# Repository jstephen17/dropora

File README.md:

# dropora
An automated system designed to securely receive and store parcels when you are away.

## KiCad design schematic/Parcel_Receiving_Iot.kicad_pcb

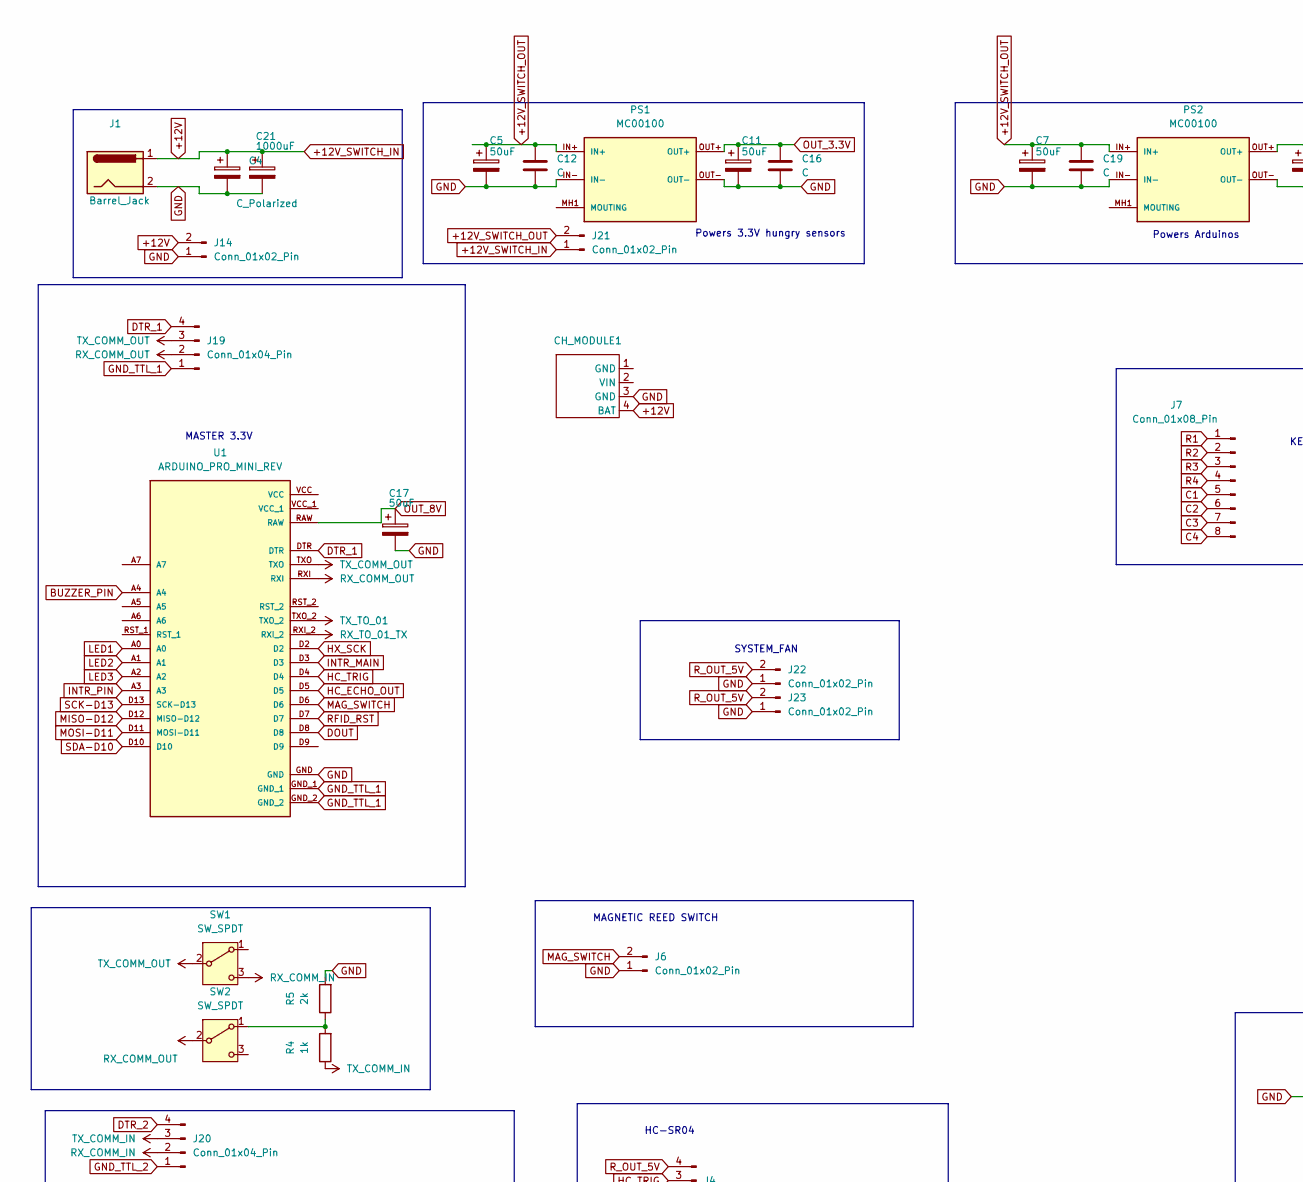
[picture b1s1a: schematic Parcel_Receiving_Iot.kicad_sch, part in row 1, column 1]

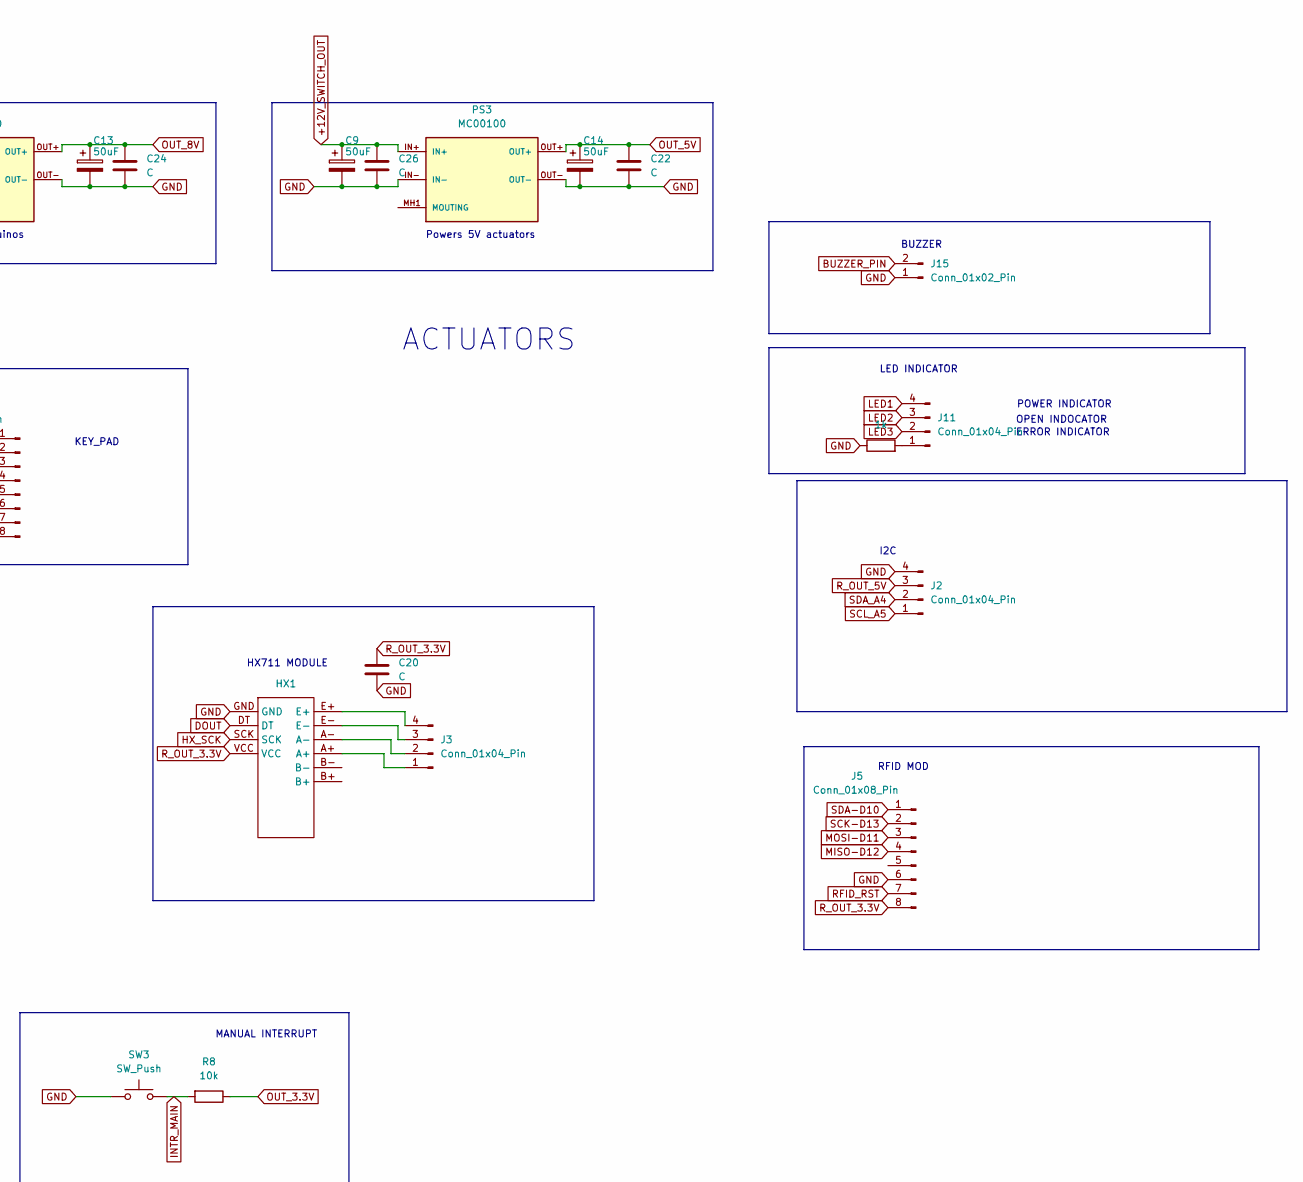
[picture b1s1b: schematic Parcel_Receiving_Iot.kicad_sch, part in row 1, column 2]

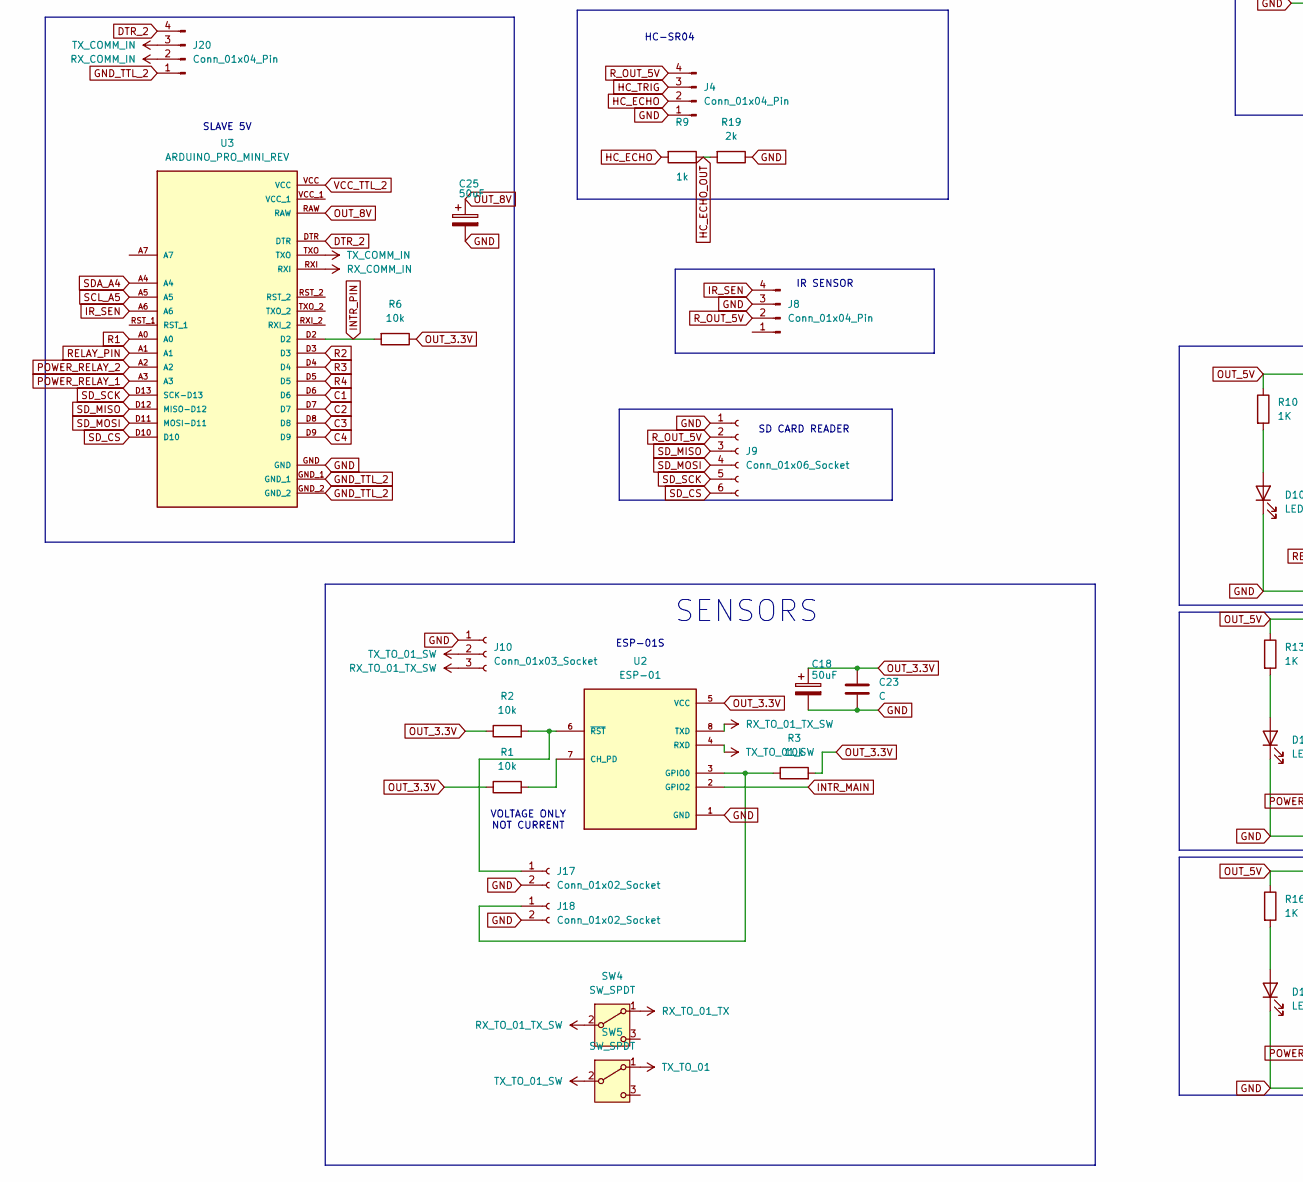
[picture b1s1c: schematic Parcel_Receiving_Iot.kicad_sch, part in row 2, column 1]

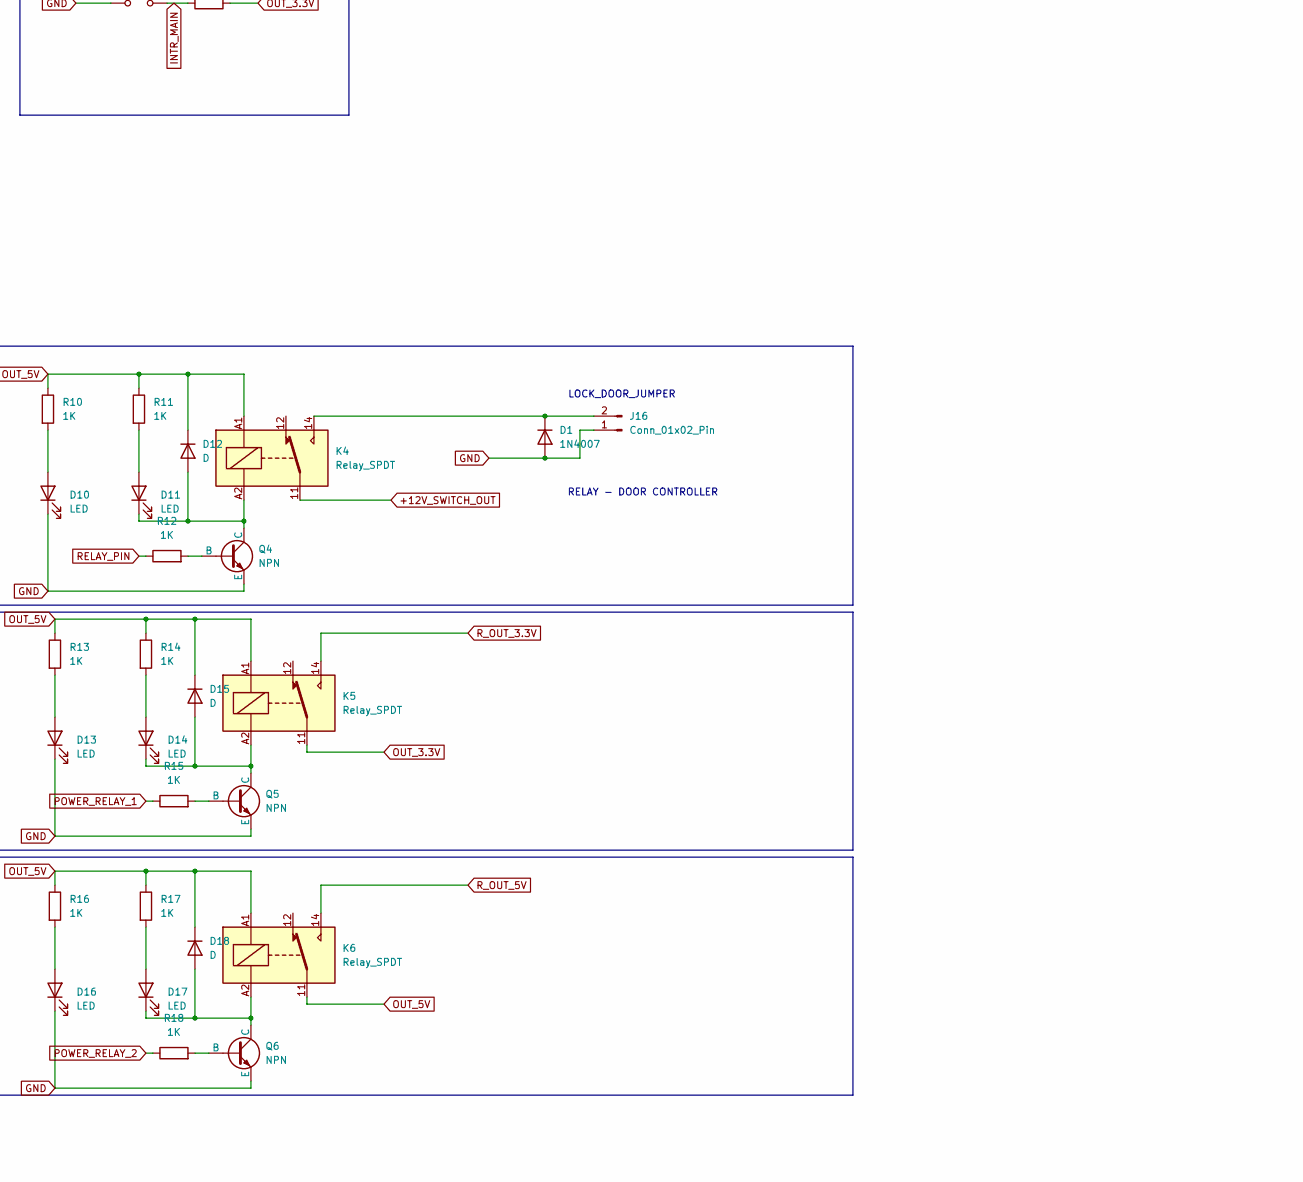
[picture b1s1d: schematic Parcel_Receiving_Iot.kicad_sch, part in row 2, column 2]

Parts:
C4: C_Polarized; CP_Radial_D5.0mm_P2.00mm
C5, C7, C9, C11, C13, C14, C18: 50uF; CP_Radial_D8.0mm_P2.50mm
C12, C16, C19, C20, C22, C23, C24, C26: C; C_Disc_D5.0mm_W2.5mm_P2.50mm
C17, C25: 50uF; CP_Radial_D5.0mm_P2.00mm
C21: 1000uF; CP_Radial_D10.0mm_P5.00mm
CH_MODULE1: CHARGING_MODULE
D1: 1N4007; D_DO-41_SOD81_P10.16mm_Horizontal
D10, D11, D13, D14, D16, D17: LED; LED_D3.0mm
D12, D15, D18: D; D_DO-15_P10.16mm_Horizontal
HX1: HX711_MODULE
J1: Barrel_Jack; BarrelJack_Horizontal
J2, J3, J4, J8, J11: Conn_01x04_Pin; JST_PH_B4B-PH-K_1x04_P2.00mm_Vertical
J5, J7: Conn_01x08_Pin; JST_PH_B8B-PH-K_1x08_P2.00mm_Vertical
J6, J15, J16: Conn_01x02_Pin; JST_PH_B2B-PH-K_1x02_P2.00mm_Vertical
J9: Conn_01x06_Socket; PinHeader_1x06_P2.54mm_Vertical
J10: Conn_01x03_Socket; PinHeader_1x03_P2.54mm_Vertical
J14, J21, J22, J23: Conn_01x02_Pin; JST_XH_B2B-XH-A_1x02_P2.50mm_Vertical
J17, J18: Conn_01x02_Socket; PinHeader_1x02_P2.54mm_Vertical
J19, J20: Conn_01x04_Pin; PinHeader_1x04_P2.54mm_Vertical
K4, K5, K6: Relay_SPDT; Relay_SPDT_SANYOU_SRD_Series_Form_C
PS1, PS2, PS3: MC00100; CONV_MC00100; PARTREV NA
Q4, Q5, Q6: NPN; TO-92L_Inline_Wide
R1, R2, R3, R6, R8: 10k; R_Axial_DIN0207_L6.3mm_D2.5mm_P10.16mm_Horizontal
R4, R7, R9: 1k; R_Axial_DIN0207_L6.3mm_D2.5mm_P10.16mm_Horizontal
R5, R19: 2k; R_Axial_DIN0207_L6.3mm_D2.5mm_P10.16mm_Horizontal
R10, R11, R12, R13, R14, R15, R16, R17, R18: 1K; R_Axial_DIN0207_L6.3mm_D2.5mm_P7.62mm_Horizontal
SW1, SW2, SW4, SW5: SW_SPDT; SW_Slide_SPDT_Straight_CK_OS102011MS2Q
SW3: SW_Push; SW_PUSH_6mm_H5mm
U1, U3: ARDUINO_PRO_MINI_REV; MODULE_ARDUINO_PRO_MINI_REV; PARTREV N/A
U2: ESP-01; MODULE_ESP-01; PARTREV 1.0

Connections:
+12V: C4.1, C21.1, CH_MODULE1.4 (BAT), J1.1, J14.2, J21.1
+12V_SWITCH_OUT: C5.1, C7.1, C9.1, C12.1, C19.1, C26.1, J21.2, K4.11, PS1.IN+, PS2.IN+, PS3.IN+
BUZZER_PIN: J15.2, U1.A4
C1: J7.5, U3.D6
C2: J7.6, U3.D7
C3: J7.7, U3.D8
C4: J7.8, U3.D9
DOUT: HX1.DT, U1.D8
DTR_1: J19.4, U1.DTR
DTR_2: J20.4, U3.DTR
GND: C4.2, C5.2, C7.2, C9.2, C11.2, C12.2, C13.2, C14.2, C16.2, C17.2, C18.2, C19.2, C20.2, C21.2, C22.2, C23.2, C24.2, C25.2, C26.2, CH_MODULE1.3 (GND), D1.2 (A), D10.1 (K), D13.1 (K), D16.1 (K), HX1.GND, J1.2, J2.4, J4.1, J5.6, J6.1, J8.3, J9.1, J10.1, J14.1, J15.1, J16.1, J17.2, J18.2, J22.1, J23.1, PS1.IN-, PS1.OUT-, PS2.IN-, PS2.OUT-, PS3.IN-, PS3.OUT-, Q4.3 (E), Q5.3 (E), Q6.3 (E), R5.2, R7.1, R19.1, SW3.1, U1.GND, U2.1 (GND), U3.GND
GND_TTL_1: J19.1, U1.GND_1, U1.GND_2
GND_TTL_2: J20.1, U3.GND_1, U3.GND_2
HC_ECHO: J4.2, R9.2
HC_ECHO_OUT: R9.1, R19.2, U1.D5
HC_TRIG: J4.3, U1.D4
HX_SCK: HX1.SCK, U1.D2
INTR_MAIN: R8.2, SW3.2, U1.D3, U2.2 (GPIO2)
INTR_PIN: R6.2, U1.A3, U3.D2
IR_SEN: J8.4, U3.A6
LED1: J11.4, U1.A0
LED2: J11.3, U1.A1
LED3: J11.2, U1.A2
MAG_SWITCH: J6.2, U1.D6
MISO-D12: J5.4, U1.D12 (MISO-D12)
MOSI-D11: J5.3, U1.D11 (MOSI-D11)
unnamed: D1.1 (K), J16.2, K4.14
unnamed: D10.2 (A), R10.2
unnamed: D11.2 (A), R11.2
unnamed: D11.1 (K), D12.2 (A), K4.A2, Q4.1 (C)
unnamed: D13.2 (A), R13.2
unnamed: D14.2 (A), R14.2
unnamed: D14.1 (K), D15.2 (A), K5.A2, Q5.1 (C)
unnamed: D16.2 (A), R16.2
unnamed: D17.2 (A), R17.2
unnamed: D17.1 (K), D18.2 (A), K6.A2, Q6.1 (C)
unnamed: HX1.A+, J3.1
unnamed: HX1.A-, J3.2
unnamed: HX1.E-, J3.3
unnamed: HX1.E+, J3.4
unnamed: J11.1, R7.2
unnamed: J17.1, R2.2, U2.6 (~RST)
unnamed: J18.1, R3.1, U2.3 (GPIO0)
unnamed: PS1.MH1 (MOUTING), PS1.MH2 (MOUTING)
unnamed: PS2.MH1 (MOUTING), PS2.MH2 (MOUTING)
unnamed: PS3.MH1 (MOUTING), PS3.MH2 (MOUTING)
unnamed: Q4.2 (B), R12.2
unnamed: Q5.2 (B), R15.2
unnamed: Q6.2 (B), R18.2
unnamed: R4.2, R5.1, SW2.1 (A)
unnamed: R1.2, U2.7 (CH_PD)
OUT_3.3V: C11.1, C16.1, C18.1, C23.1, K5.11, PS1.OUT+, R1.1, R2.1, R3.2, R6.1, R8.1, U2.5 (VCC)
OUT_5V: C14.1, C22.1, D12.1 (K), D15.1 (K), D18.1 (K), K4.A1, K5.A1, K6.11, K6.A1, PS3.OUT+, R10.1, R11.1, R13.1, R14.1, R16.1, R17.1
OUT_8V: C13.1, C17.1, C24.1, C25.1, PS2.OUT+, U1.RAW, U3.RAW
POWER_RELAY_1: R15.1, U3.A3
POWER_RELAY_2: R18.1, U3.A2
R1: J7.1, U3.A0
R2: J7.2, U3.D3
R3: J7.3, U3.D4
R4: J7.4, U3.D5
RELAY_PIN: R12.1, U3.A1
RFID_RST: J5.7, U1.D7
RX_COMM_IN: J20.2, SW1.3 (C), U3.RXI
RX_COMM_OUT: J19.2, SW2.2 (B), U1.RXI
RX_TO_01_TX: SW4.1 (A), U1.RXI_2
RX_TO_01_TX_SW: J10.3, SW4.2 (B), U2.8 (TXD)
R_OUT_3.3V: C20.1, HX1.VCC, J5.8, K5.14
R_OUT_5V: J2.3, J4.4, J8.2, J9.2, J22.2, J23.2, K6.14
SCK-D13: J5.2, U1.D13 (SCK-D13)
SCL_A5: J2.1, U3.A5
SDA-D10: J5.1, U1.D10
SDA_A4: J2.2, U3.A4
SD_CS: J9.6, U3.D10
SD_MISO: J9.3, U3.D12 (MISO-D12)
SD_MOSI: J9.4, U3.D11 (MOSI-D11)
SD_SCK: J9.5, U3.D13 (SCK-D13)
TX_COMM_IN: J20.3, R4.1, U3.TXO
TX_COMM_OUT: J19.3, SW1.2 (B), U1.TXO
TX_TO_01: SW5.1 (A), U1.TXO_2
TX_TO_01_SW: J10.2, SW5.2 (B), U2.4 (RXD)
VCC_TTL_2: U3.VCC

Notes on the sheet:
HX711 MODULE
MANUAL INTERRUPT
SENSORS
POWER INDICATOR
ERROR INDICATOR
SD CARD READER
ACTUATORS
SYSTEM_FAN
MASTER 3.3V
Powers Arduinos
HC-SR04
OPEN INDOCATOR
LOCK_DOOR_JUMPER
KEY_PAD
SLAVE 5V
Powers 3.3V hungry sensors
BUZZER
VOLTAGE ONLY NOT CURRENT
RFID MOD
I2C
RELAY - DOOR CONTROLLER
MAGNETIC REED SWITCH
ESP-01S
IR SENSOR
Powers 5V actuators
LED INDICATOR

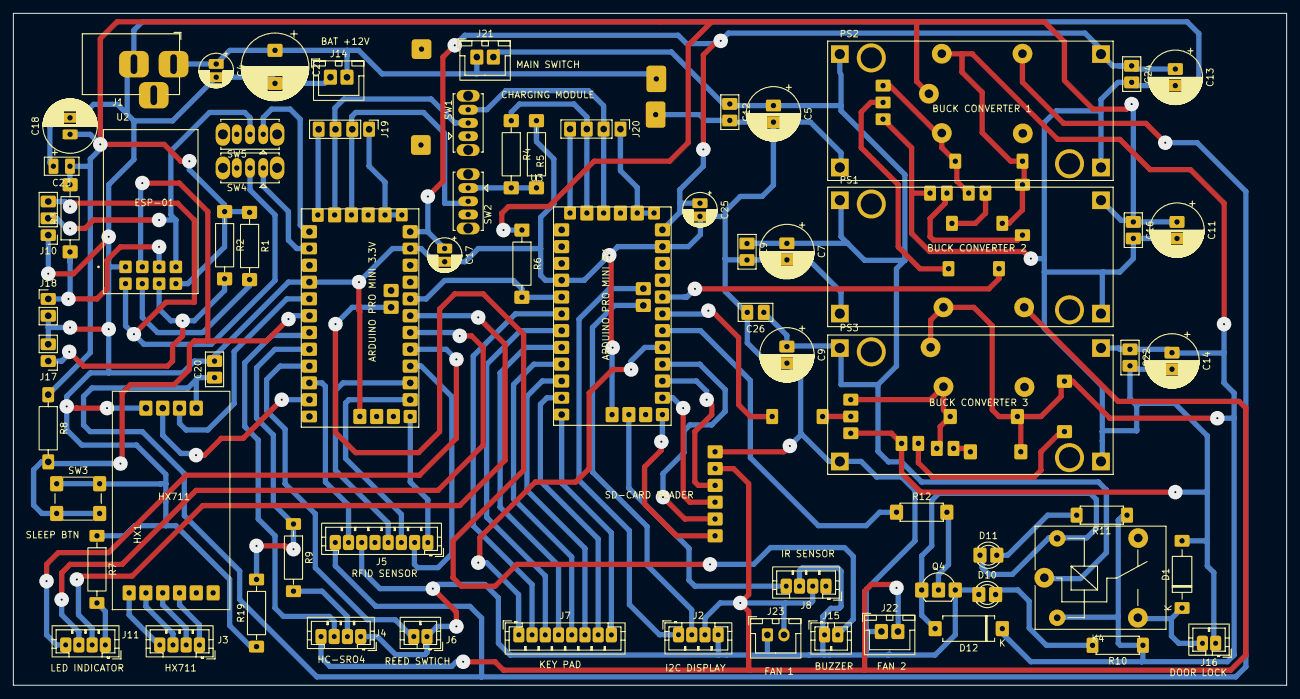
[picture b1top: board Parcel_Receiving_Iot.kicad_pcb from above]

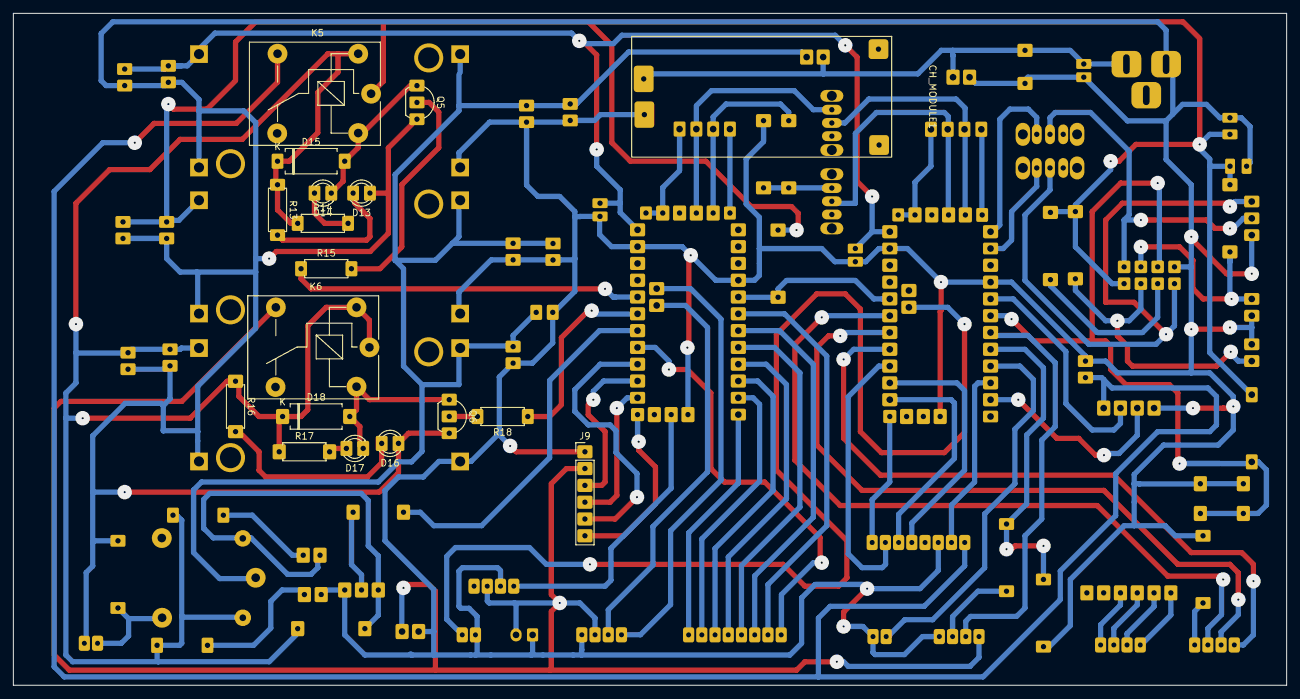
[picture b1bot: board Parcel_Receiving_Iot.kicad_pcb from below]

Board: 2 copper layers, 192.5 x 101.6 mm, 88 parts (18 on the bottom side), 80 nets.
